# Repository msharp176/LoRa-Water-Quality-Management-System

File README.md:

# LoRa Water Quality Management System
### By Cole Hadley, Patricio Benitez Palermo, and Matthew Sharp
#### Penn State Harrisburg Senior Electrical Engineering Capstone Design Course, Fall 2025

# Project Repository Overview

This repository contains all hardware, firmware, software, and documentation associated with the gateway, sensor node, and supporting prototypes used throughout this project. The directory structure is organized to clearly separate production-ready components from prototyping artifacts, while providing comprehensive traceability for PCB designs, firmware, simulations, and supporting tools.

## Directory Structure

### **Gateway**

Code and PCB designs for the system gateway.

* **Dashboard**
  Python code for the gateway dashboard and system monitoring utilities.

* **LoRa Receiver**
  PCB design files, RP2350 firmware, and a console-logging Python script for a dedicated LoRa receiver module.

* **Neural Network**
  Code and related resources for the neural network implementation used in the system.

---

### **Prototyping and Testing**

Various PCB designs and test code used during early prototyping and validation phases.

---

### **Sensor Node**

Master directory for the final Sensor Node design, including PCB files, firmware, documentation, and test artifacts.

#### **Code**

Production firmware implementation for the Sensor Node.

* **Bin**
  Final binary executable for the RP2350 microcontroller (`.uf2`).

* **Lib**
  Custom-implemented C drivers for the sensor node.

  * **sx126x**: Semtech-provided driver files with custom HAL and radio ISR implementations.

* **Stash**
  Top-level gateway/node firmware source files. These are not included in the build unless a file is manually integrated into `main.c`.

* **Sys_Utils**
  Abstracted system-level modules, including LoRa communications, RDT3.0 implementation, and other project-specific utilities.

* **Tests**
  Code used to validate custom drivers and subsystem behaviors.

#### **Docs**

Datasheets, PCB design write-ups, and annotated Bill-of-Materials (BOM) for the final Sensor Node PCB.

#### **PCB Layout**

Complete KiCAD implementation of the sensor node PCB.

#### **Simulation**

Simulation files and output results for the analyses performed during development.

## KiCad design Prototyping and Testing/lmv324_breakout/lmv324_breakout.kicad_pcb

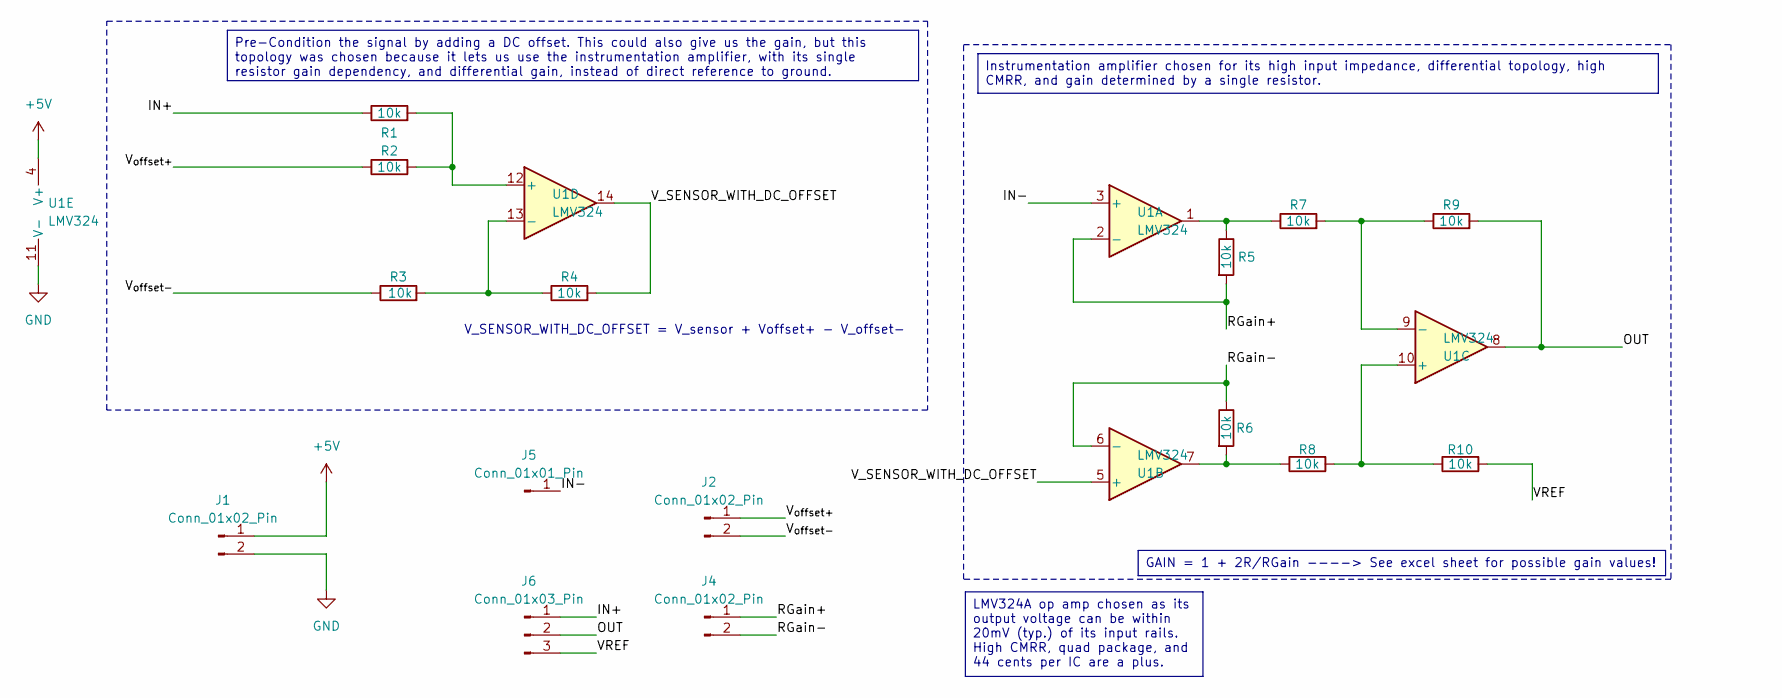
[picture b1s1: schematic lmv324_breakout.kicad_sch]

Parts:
J1, J2, J4: Conn_01x02_Pin; PinHeader_1x02_P2.54mm_Vertical
J5: Conn_01x01_Pin; PinHeader_1x01_P2.54mm_Vertical
J6: Conn_01x03_Pin; PinHeader_1x03_P2.54mm_Vertical
R1, R2, R3, R4, R5, R6, R7, R8, R9, R10: 10k; R_0805_2012Metric_Pad1.20x1.40mm_HandSolder
U1: LMV324; TSSOP-14_4.4x5mm_P0.65mm

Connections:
+5V: J1.1, U1.4 (V+)
/IN+: J6.1, R1.1
/IN-: J5.1, U1.3 (+)
/OUT: J6.2, R9.2, U1.8
/RGain+: J4.1, R5.2, U1.2 (-)
/RGain-: J4.2, R6.1, U1.6 (-)
/VREF: J6.3, R10.2
/V_SENSOR_WITH_DC_OFFSET: R4.2, U1.5 (+), U1.14
/V_{offset+}: J2.1, R2.1
/V_{offset-}: J2.2, R3.1
GND: J1.2, U1.11 (V-)
unnamed: R5.1, R7.1, U1.1
unnamed: R6.2, R8.1, U1.7
unnamed: R8.2, R10.1, U1.10 (+)
unnamed: R7.2, R9.1, U1.9 (-)
unnamed: R1.2, R2.2, U1.12 (+)
unnamed: R3.2, R4.1, U1.13 (-)

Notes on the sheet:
V_SENSOR_WITH_DC_OFFSET = V_sensor + Voffset+ - V_offset-
Instrumentation amplifier chosen for its high input impedance, differential topology, high CMRR, and gain determined by a single resistor.
Pre-Condition the signal by adding a DC offset. This could also give us the gain, but this topology was chosen because it lets us use the instrumentation amplifier, with its single resistor gain dependency, and differential gain, instead of direct reference to ground.
LMV324A op amp chosen as its output voltage can be within 20mV (typ.) of its input rails. High CMRR, quad package, and 44 cents per IC are a plus.
GAIN = 1 + 2R/RGain ----> See excel sheet for possible gain values!

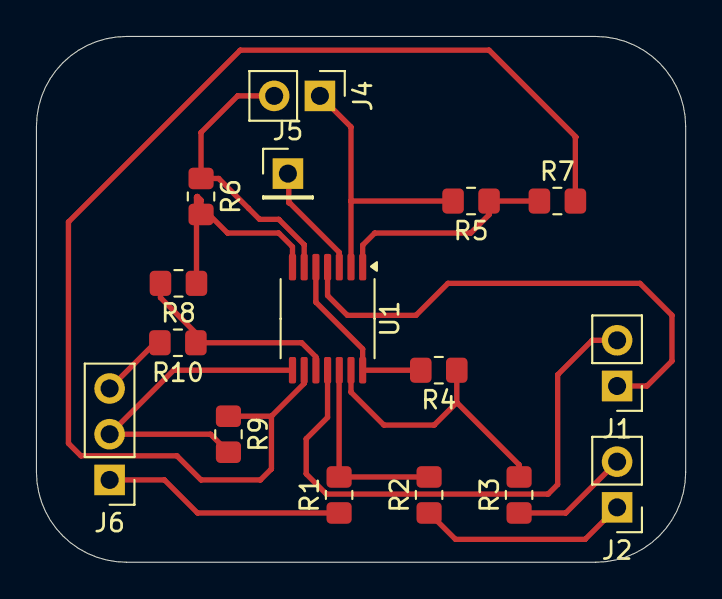
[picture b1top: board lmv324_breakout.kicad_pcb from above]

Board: 2 copper layers, 36.1 x 29.2 mm, 16 parts (0 on the bottom side), 17 nets.

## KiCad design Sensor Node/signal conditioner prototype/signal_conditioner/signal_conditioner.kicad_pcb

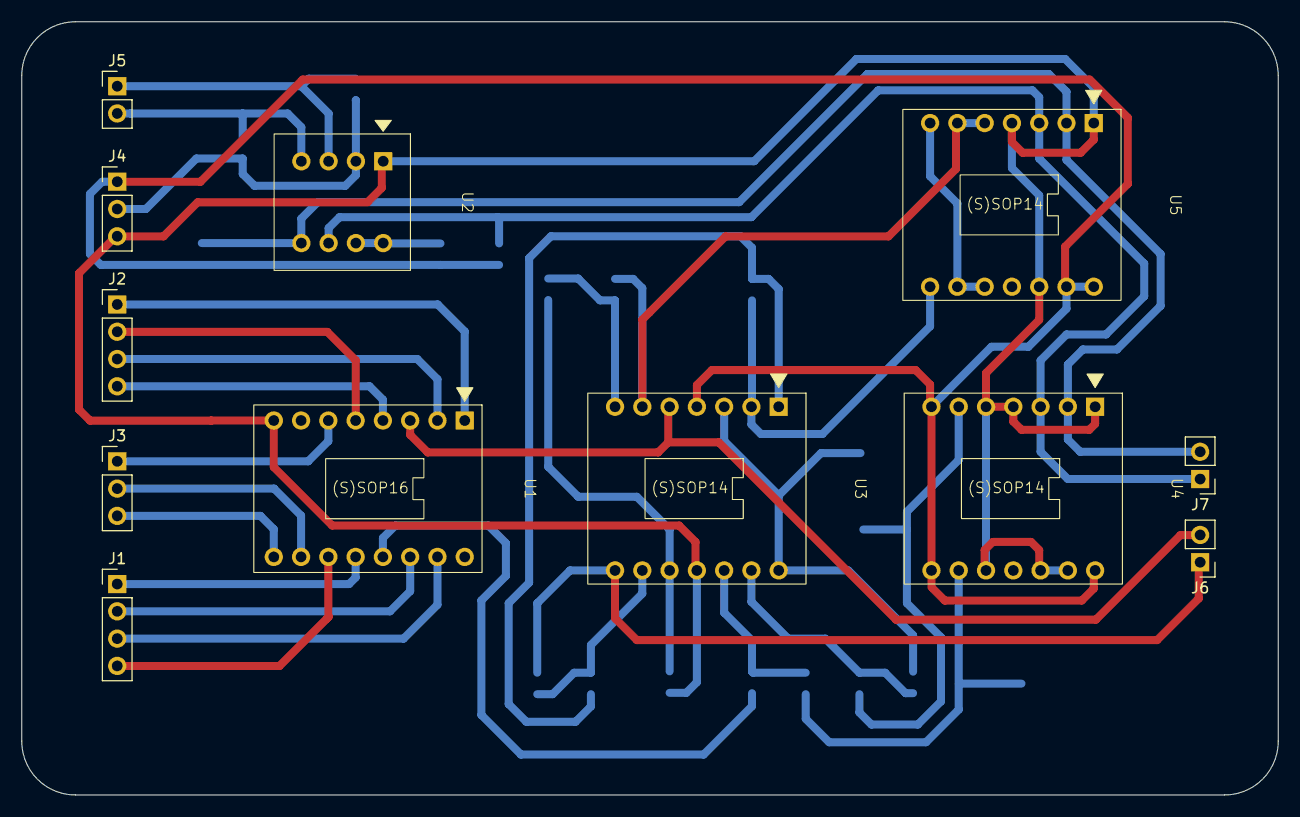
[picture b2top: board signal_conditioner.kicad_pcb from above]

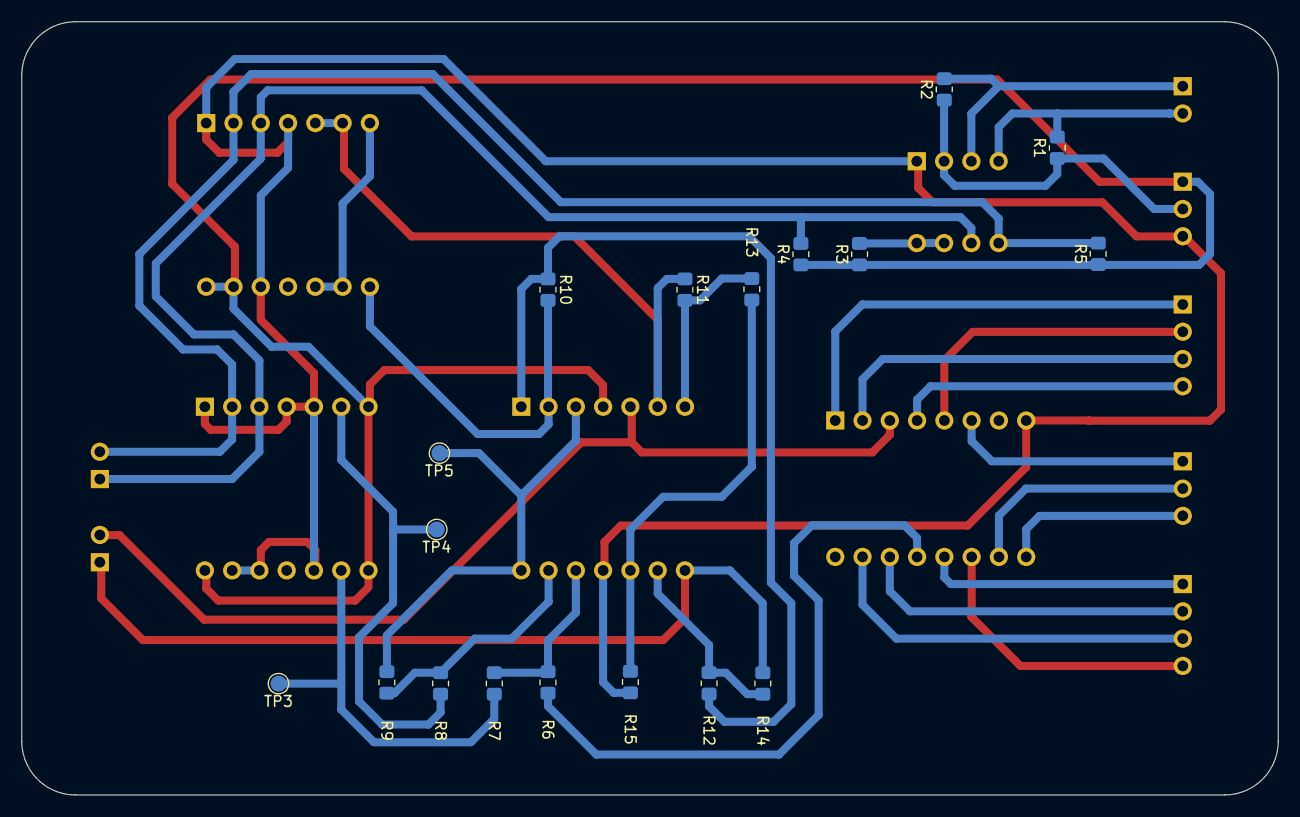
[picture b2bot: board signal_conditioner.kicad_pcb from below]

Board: 2 copper layers, 117.0 x 72.0 mm, 30 parts (18 on the bottom side), 34 nets.

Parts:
J1, J2: Conn_01x04_Pin; PinHeader_1x04_P2.54mm_Vertical
J3, J4: Conn_01x03_Pin; PinHeader_1x03_P2.54mm_Vertical
J5, J6, J7: Conn_01x02_Pin; PinHeader_1x02_P2.54mm_Vertical
R1, R2, R4, R5: 4k; R_0805_2012Metric_Pad1.20x1.40mm_HandSolder
R3: 200k; R_0805_2012Metric_Pad1.20x1.40mm_HandSolder
R6, R7, R8, R9, R10, R11, R12, R13, R14, R15: 10k; R_0805_2012Metric_Pad1.20x1.40mm_HandSolder
TP3, TP4, TP5: TestPoint_Small; TestPoint_Pad_D1.5mm
U1: TMUX1309; (S)SOP16
U2: LSF0102; (S)SOP8
U3: LMV324; (S)SOP14
U4, U5: MCP4651T-503E_ST; (S)SOP14

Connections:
+3V3: J4.2, R1.1, R2.1, U2.2 (Vref_{A})
+5V: J4.1, R3.1, R4.1, R5.1, U3.4 (V+), U4.7 (P1A), U4.8 (P0A), U4.14 (VDD), U5.13 (A1), U5.14 (VDD)
/I2C_SCL_{1}: J5.2, R1.2, U2.4 (A_{2})
/I2C_SCL_{1}_5V: J7.2, R5.2, U2.5 (B2), U4.2 (SCL), U5.2 (SCL)
/I2C_SDA_{1}: J5.1, R2.2, U2.3 (A_{1})
/I2C_SDA_{1}_5V: J7.1, R4.2, U2.6 (B1), U4.3 (SDA), U5.3 (SDA)
/OUT+: J6.1, R14.2, U3.8
/OUT-: J6.2, U1.3 (DB), U3.5 (+)
/S0A: J1.1, U1.12 (S0A)
/S0B: J2.1, U1.1 (S0B)
/S1A: J1.2, U1.14 (S1A)
/S1B: J2.2, U1.5 (S1B)
/S2A: J1.3, U1.15 (S2A)
/S2B: J2.3, U1.2 (S2B)
/S3A: J1.4, U1.11 (S3A)
/S3B: J2.4, U1.4 (S3B)
/SEL0: J3.2, U1.10 (A0)
/SEL1: J3.3, U1.9 (A1)
/SEN+: R6.1, U1.13 (DA)
/Software Defined Instrumentation Amplifier/RGain+: R10.2, U3.2 (-), U5.8 (P0A)
/Software Defined Instrumentation Amplifier/RGain-: R11.1, U3.6 (-), U5.5 (P1B), U5.6 (P1W)
/Software Defined Instrumentation Amplifier/V_SENSOR_WITH_DC_OFFSET: R9.2, TP5.1, U3.3 (+), U3.14
/Software Defined Instrumentation Amplifier/V_{offset+}: R7.1, TP3.1, U4.9 (P0W)
/Software Defined Instrumentation Amplifier/V_{offset-}: R8.1, TP4.1, U4.6 (P1W)
/~EN: J3.1, U1.6 (~EN)
GND: J4.3, R15.2, U1.8 (GND), U2.1 (GND), U3.11 (V-), U4.1 (HVC/A0), U4.4 (VSS), U4.5 (P1B), U4.10 (P0B), U4.12 (A2), U4.13 (A1), U5.1 (HVC/A0), U5.4 (VSS), U5.12 (A2)
unnamed: R10.1, R12.1, U3.1
unnamed: R11.2, R13.1, U3.7
unnamed: R3.2, U2.7 (Vref_{B}), U2.8 (EN)
unnamed: R13.2, R15.1, U3.10 (+)
unnamed: R12.2, R14.1, U3.9 (-)
unnamed: R6.2, R7.2, U3.12 (+)
unnamed: R8.2, R9.1, U3.13 (-)
unnamed: U5.7 (P1A), U5.9 (P0W), U5.10 (P0B)

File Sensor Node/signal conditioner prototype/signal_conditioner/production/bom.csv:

Designator,Footprint,Quantity,Value,LCSC Part #
"J1, J2",PinHeader_1x04_P2.54mm_Vertical,2,Conn_01x04_Pin,
"J3, J4",PinHeader_1x03_P2.54mm_Vertical,2,Conn_01x03_Pin,
"J5, J6, J7",PinHeader_1x02_P2.54mm_Vertical,3,Conn_01x02_Pin,
"R1, R2, R4, R5",0805,4,4k,
"R10, R11, R12, R13, R14, R15, R6, R7, R8, R9",0805,10,10k,
R3,0805,1,200k,
"TP3, TP4, TP5",TestPoint_Pad_D1.5mm,3,TestPoint_Small,
U1,(S)SOP16,1,TMUX1309,
U2,(S)SOP8,1,LSF0102,
U3,(S)SOP14,1,LMV324,
"U4, U5",(S)SOP14,2,MCP4651T-503E_ST,

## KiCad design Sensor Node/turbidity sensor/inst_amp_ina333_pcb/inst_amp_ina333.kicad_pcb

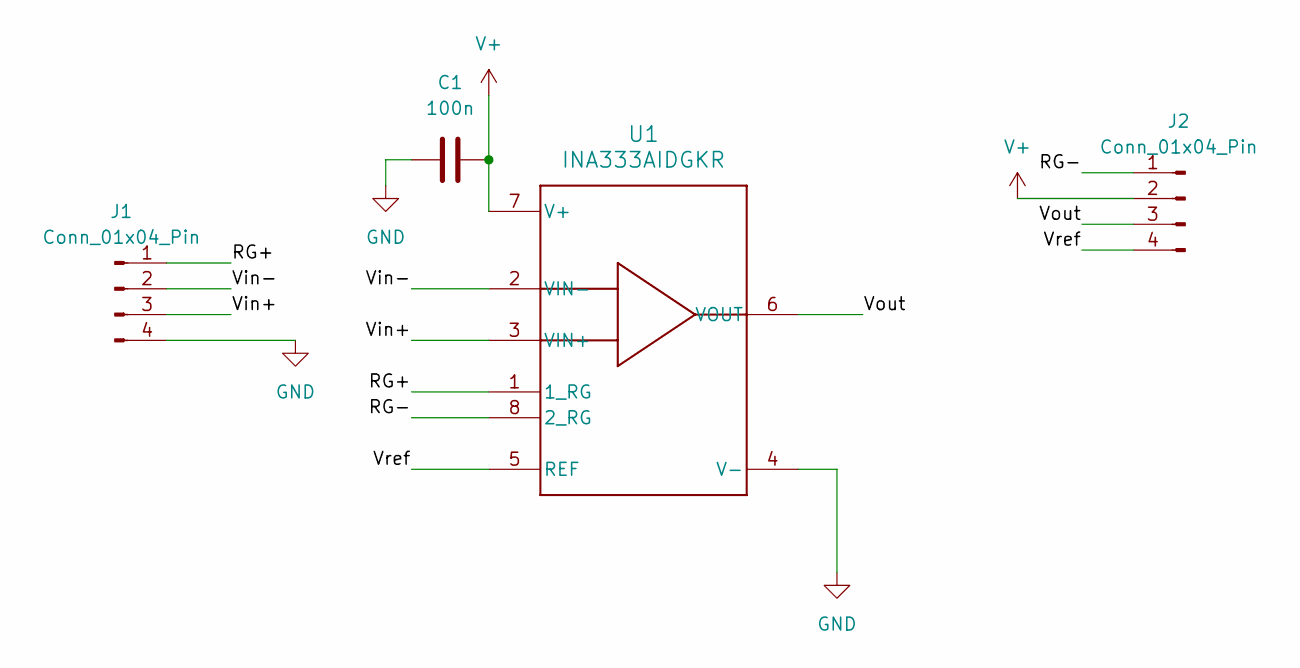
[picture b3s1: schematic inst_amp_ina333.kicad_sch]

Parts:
C1: 100n; C_1206_3216Metric
J1, J2: Conn_01x04_Pin; PinHeader_1x04_P2.54mm_Vertical
U1: INA333AIDGKR; INA333_VSSOP

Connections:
/RG+: J1.1, U1.1 (1_RG)
/RG-: J2.1, U1.8 (2_RG)
/Vin+: J1.3, U1.3 (VIN+)
/Vin-: J1.2, U1.2 (VIN-)
/Vout: J2.3, U1.6 (VOUT)
/Vref: J2.4, U1.5 (REF)
GND: C1.1, J1.4, U1.4 (V-)
V+: C1.2, J2.2, U1.7 (V+)

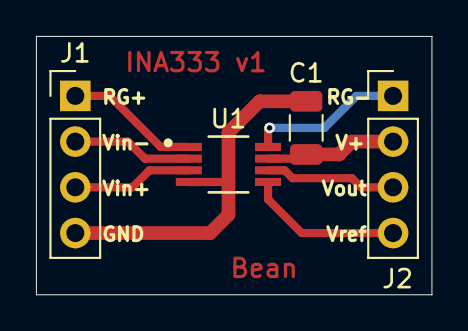
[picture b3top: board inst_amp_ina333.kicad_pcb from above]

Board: 2 copper layers, 22.0 x 14.4 mm, 4 parts (0 on the bottom side), 8 nets.

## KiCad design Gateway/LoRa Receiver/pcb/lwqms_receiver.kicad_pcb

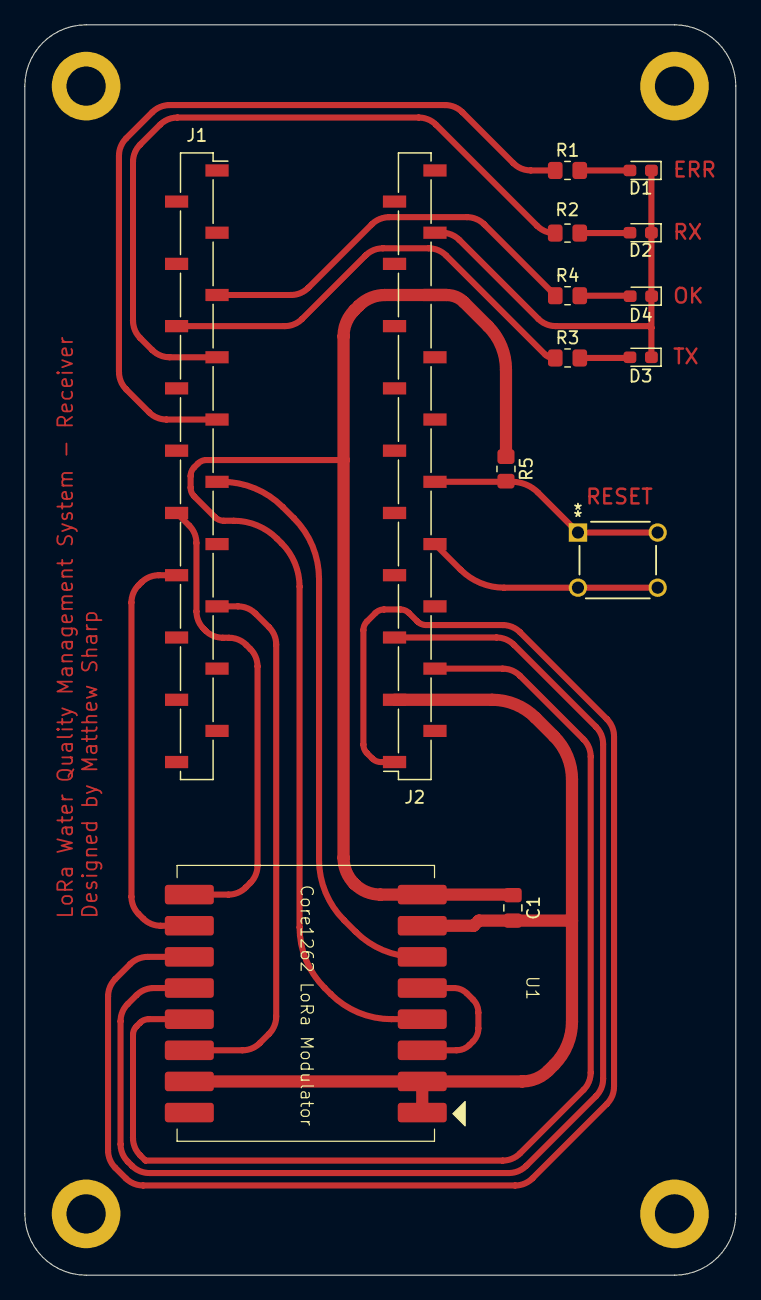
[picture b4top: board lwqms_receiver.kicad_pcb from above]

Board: 2 copper layers, 58.0 x 102.0 mm, 14 parts (0 on the bottom side), 21 nets.

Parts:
C1: 100n; C_0805_2012Metric_Pad1.18x1.45mm_HandSolder
D1, D2, D3, D4: LED; LED_0603_1608Metric_Pad1.05x0.95mm_HandSolder
J1, J2: Conn_01x20; PinSocket_1x20_P2.54mm_Vertical_SMD_Pin1Right
R1: 75R; R_0805_2012Metric_Pad1.20x1.40mm_HandSolder
R2, R3, R4: 165R; R_0805_2012Metric_Pad1.20x1.40mm_HandSolder
R5: 10k; R_0805_2012Metric_Pad1.20x1.40mm_HandSolder
SW1: Tactile Pushbutton; SW4_1825910-B_TEC
U1: Core1262 HF; Core1262

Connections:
+3V3: C1.1, J2.16, R5.1, U1.4 (TXEN), U1.8 (V_{DD})
/ERR_LED: J1.9, R1.1
/LoRa_BUSY: J1.12, U1.9 (BUSY)
/LoRa_CS: J1.15, U1.14 (~CS)
/LoRa_IRQ: J1.11, U1.6 (DIO1)
/LoRa_~RESET: J1.14, U1.10 (~RESET)
/RX_LED: J1.7, R2.1
/SPI_MISO_{0}: J2.1, U1.11 (MISO)
/SPI_MOSI_{0}: J2.5, U1.12 (MOSI)
/SPI_SCK_{0}: J2.4, U1.13 (SCK)
/STATUS_LED: J1.5, R4.1
/TX_LED: J1.6, R3.1
GND: C1.2, J2.3, U1.1 (GND), U1.2 (GND), U1.7 (GND), U1.15 (GND)
GND1: J2.8, SW1.3 (B1), SW1.4 (B2)
GND2: D1.1 (K), D2.1 (K), D3.1 (K), D4.1 (K), J2.18
unnamed: D1.2 (A), R1.2
unnamed: D2.2 (A), R2.2
unnamed: D3.2 (A), R3.2
unnamed: D4.2 (A), R4.2
unnamed: J2.10, R5.2, SW1.1 (A1), SW1.2 (A2)
unnamed: U1.3 (RXEN), U1.5 (DIO2)

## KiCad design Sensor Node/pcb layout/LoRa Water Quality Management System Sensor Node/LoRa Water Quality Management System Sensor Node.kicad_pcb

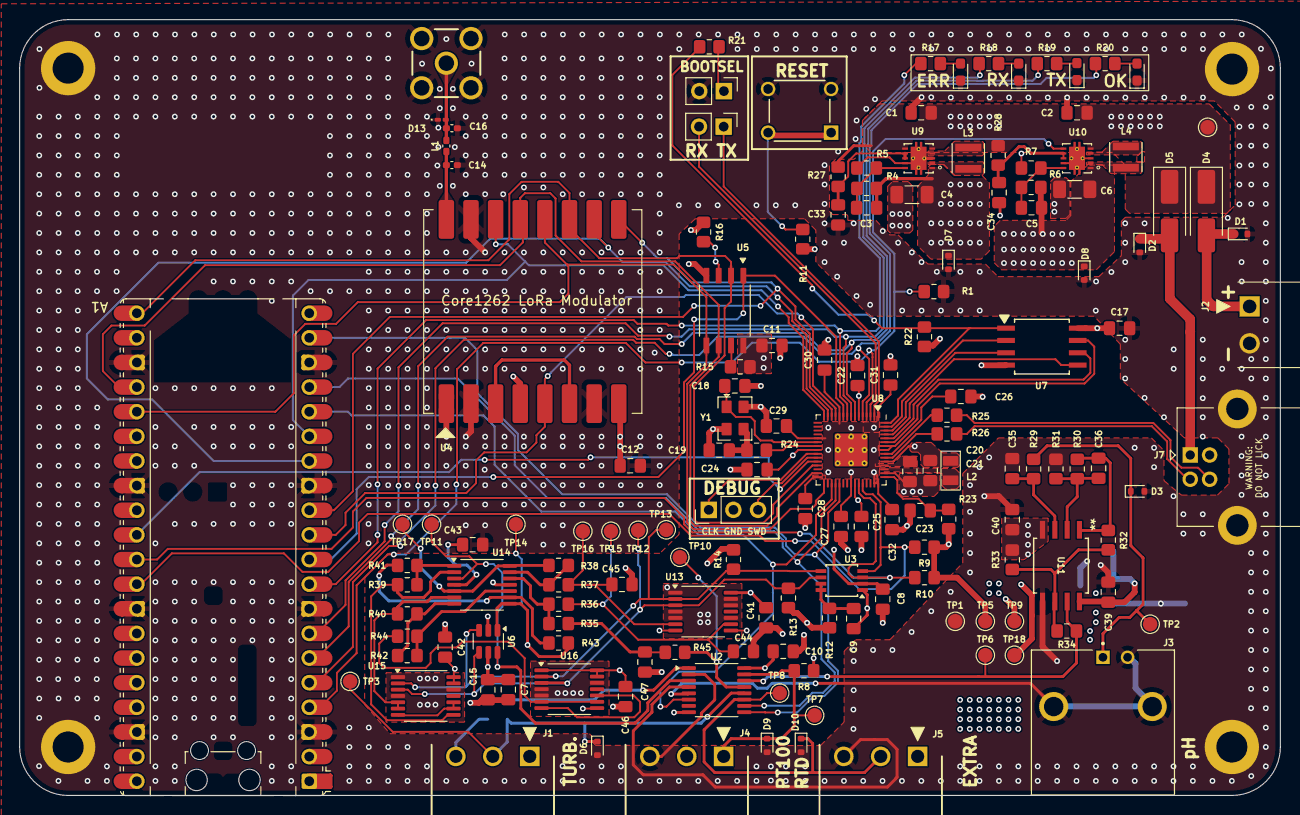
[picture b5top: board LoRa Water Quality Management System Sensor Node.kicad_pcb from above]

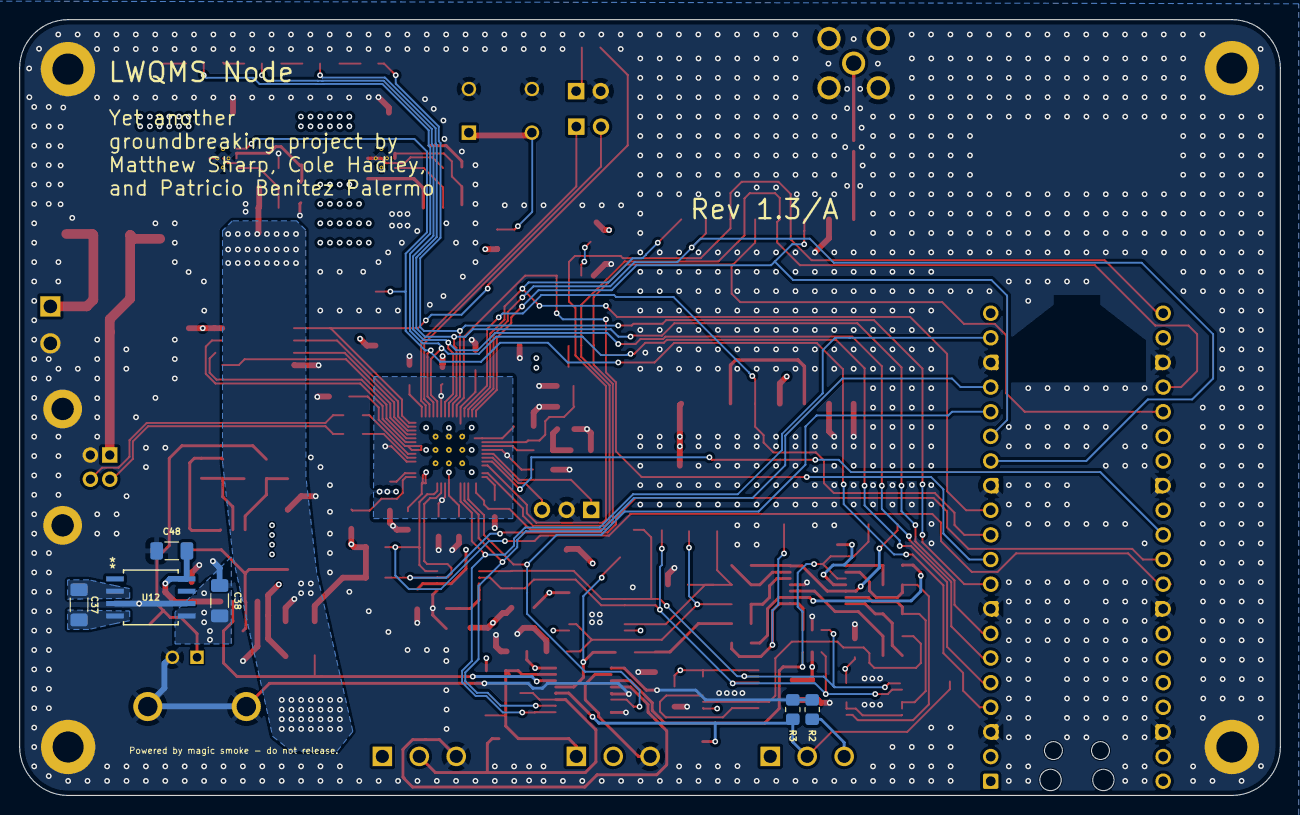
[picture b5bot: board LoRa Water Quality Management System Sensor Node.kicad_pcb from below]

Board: 4 copper layers, 130.0 x 80.0 mm, 157 parts (6 on the bottom side), 96 nets.

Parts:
A1: RaspberryPi_Pico; RaspberryPi_Pico_Common_Unspecified
C1, C2: 22uF; C_0805_2012Metric_Pad1.18x1.45mm_HandSolder
C3: 4p; C_0805_2012Metric_Pad1.18x1.45mm_HandSolder
C4, C6: 47uF; C_1206_3216Metric_Pad1.33x1.80mm_HandSolder
C5: 2.4p; C_0805_2012Metric_Pad1.18x1.45mm_HandSolder
C7, C20, C21, C23, C24: 4.7u; C_0805_2012Metric_Pad1.18x1.45mm_HandSolder
C8, C9, C10, C11, C12, C15, C17, C22, C25, C26, C27, C28, C29, C30, C31, C32, C33, C34, C39, C40, C41, C42, C43, C44, C45, C46, C47: 100n; C_0805_2012Metric_Pad1.18x1.45mm_HandSolder
C14, C16: C; C_0402_1005Metric_Pad0.74x0.62mm_HandSolder
C18, C19: 15p; C_0805_2012Metric_Pad1.18x1.45mm_HandSolder
C35: 2.2n; C_0805_2012Metric_Pad1.18x1.45mm_HandSolder
C36: 1u; C_0805_2012Metric_Pad1.18x1.45mm_HandSolder
C37, C38, C48: 100u; C_1206_3216Metric_Pad1.33x1.80mm_HandSolder
D1, D2, D3, D6, D8, D9, D10: T5V0S5A-7; D_SOD-523
D4, D5: B240AE-13; D_SMA_Handsoldering
D7: T3V3S5A-7; D_SOD-523
D11, D12, D14, D15: LED; LED_0603_1608Metric_Pad1.05x0.95mm_HandSolder
D13: ESDARF02-1BU2CK; D_0201_0603Metric_Pad0.64x0.40mm_HandSolder
J1, J4, J5: OQ0332510000G
J2: OQ0232510000G
J3: CONBNC002; LINX_CONBNC002
J6, J9: Conn_01x02; PinHeader_1x02_P2.54mm_Vertical
J7: USB_B; USB_B_Lumberg_2411_02_Horizontal
J8: SMA-J-P-X-RA-TH1; SAMTEC_SMA-J-P-X-RA-TH1
J10: Conn_01x03; PinHeader_1x03_P2.54mm_Vertical
L1: L; L_0402_1005Metric_Pad0.77x0.64mm_HandSolder
L2: 3.3u; AOTA-B201610S3R3-101-T
L3, L4: 2.2uH; IND_LQH3NPZ2R2MMEL
R1, R5, R7: 100k; R_0805_2012Metric_Pad1.20x1.40mm_HandSolder
R2: 0R; R_0805_2012Metric_Pad1.20x1.40mm_HandSolder
R3, R8: 4.7k; R_0805_2012Metric_Pad1.20x1.40mm_HandSolder
R4: 560k; R_0805_2012Metric_Pad1.20x1.40mm_HandSolder
R6: 910k; R_0805_2012Metric_Pad1.20x1.40mm_HandSolder
R9, R10, R13, R14, R21, R24: 1k; R_0805_2012Metric_Pad1.20x1.40mm_HandSolder
R11, R15, R16, R22, R30, R31, R33, R39, R40, R41, R42, R43, R44: 10k; R_0805_2012Metric_Pad1.20x1.40mm_HandSolder
R12: 200k; R_0805_2012Metric_Pad1.20x1.40mm_HandSolder
R17: 75R; R_0805_2012Metric_Pad1.20x1.40mm_HandSolder
R18, R19, R20: 165R; R_0805_2012Metric_Pad1.20x1.40mm_HandSolder
R23: 33R; R_0805_2012Metric_Pad1.20x1.40mm_HandSolder
R25, R26: 27R; R_0805_2012Metric_Pad1.20x1.40mm_HandSolder
R27, R28, R45: 100R; R_0805_2012Metric_Pad1.20x1.40mm_HandSolder
R29: 4.7M; R_0805_2012Metric_Pad1.20x1.40mm_HandSolder
R32, R34: 4.99k; R_0805_2012Metric_Pad1.20x1.40mm_HandSolder
R35, R36, R37, R38: 3.3M; R_0805_2012Metric_Pad1.20x1.40mm_HandSolder
SW1: Tactile Pushbutton; SW4_1825910-B_TEC
TP1, TP2, TP3, TP4, TP5, TP6, TP7, TP8, TP9, TP10, TP11, TP12, TP13, TP14: TestPoint; TestPoint_Pad_D1.5mm
TP15, TP16, TP17, TP18: TestPoint_Small; TestPoint_Pad_D1.5mm
U2: TMUX1309; TSSOP-16_4.4x5mm_P0.65mm
U3: LSF0102; TSSOP-8_3x3mm_P0.65mm
U4: Core1262 HF; Core1262
U5: MX25L3233FM2I-08Q; SOIC127P790X216-8N
U6: MCP3425Axx-xCH; SOT-23-6
U7: W25Q128JVSIQ TR; SOIC_208MIL_WIN-M
U8: RP2350_60QFN; RP2350-QFN-60-1EP_7x7_P0.4mm_EP3.4x3.4mm_ThermalVias
U9, U10: TPS63000; CONV_TPS63000DRCR
U11: TL082; SOIC_208MIL_WIN-M
U12: LM2660MX; SOIC_208MIL_WIN-M
U13, U15, U16: MCP4651T-503E_ST; TSSOP-14_4.4x5mm_P0.65mm
U14: TLV9144; TSSOP-14_4.4x5mm_P0.65mm
Y1: ABM8-272-T3

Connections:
+1V1: C21.1, C22.1, C24.1, C25.1, L2.1, U8.6 (DVDD), U8.23 (DVDD), U8.39 (DVDD), U8.50 (VREG_FB)
+3V3: A1.39 (VSYS), C3.1, C4.1, C8.1, C11.1, C12.1, C17.1, C20.1, C26.1, C27.1, C28.1, C29.1, C30.1, C31.1, C32.1, D7.1 (K), R4.1, R9.1, R10.1, R11.1, R15.1, R16.1, R22.1, R23.1, TP5.1, U3.2 (Vref_{A}), U4.4 (TXEN), U4.8 (V_{DD}), U5.8 (V_{CC}), U7.8 (VCC), U8.1 (IOVDD), U8.11 (IOVDD), U8.20 (IOVDD), U8.30 (IOVDD), U8.38 (IOVDD), U8.44 (ADC_AVDD), U8.45 (IOVDD), U8.49 (VREG_VIN), U8.53 (USB_OTP_VDD), U8.54 (QSPI_IOVDD), U9.1 (VOUT)
+5V: C5.1, C6.1, C7.1, C10.1, C15.1, C39.1, C41.2, C42.2, C43.1, C46.2, C48.1, D8.1 (K), J1.1, J5.1, R6.1, R8.1, R12.1, R13.1, R14.1, TP9.1, U2.16 (V_{DD}), U6.5 (V_{DD}), U10.1 (VOUT), U11.8 (V+), U12.8 (V+), U13.7 (P1A), U13.8 (P0A), U13.14 (VDD), U14.4 (V+), U15.13 (A1), U15.14 (VDD), U16.1 (HVC/A0), U16.8 (P0A), U16.13 (A1), U16.14 (VDD)
/5V_EN: A1.4 (GPIO2), R1.1, U8.4 (GPIO2), U10.6 (EN)
/Buck-Boost Regulator Layout1/FB: C5.2, R6.2, R7.1, U10.10 (FB)
/Buck-Boost Regulator Layout/FB: C3.2, R4.2, R5.1, U9.10 (FB)
/ERR_LED: A1.9 (GPIO6), R17.1, U8.9 (GPIO6)
/EXTRA_IN: D10.1 (K), J5.2, TP8.1, U2.11 (S3A)
/I2C_SCL_{1}: A1.32 (GPIO27_ADC1), R9.2, U3.4 (A_{2}), U8.41 (GPIO27_ADC1)
/I2C_SCL_{1}_5V: R14.2, TP13.1, U3.5 (B2), U6.3 (SCL), U13.2 (SCL), U15.2 (SCL), U16.2 (SCL)
/I2C_SDA_{1}: A1.31 (GPIO26_ADC0), R10.2, U3.3 (A_{1}), U8.40 (GPIO26_ADC0)
/I2C_SDA_{1}_5V: R13.2, TP12.1, U3.6 (B1), U6.4 (SDA), U13.3 (SDA), U15.3 (SDA), U16.3 (SDA)
/LoRa_BUSY: A1.12 (GPIO9), U4.9 (BUSY), U8.13 (GPIO9)
/LoRa_CS: A1.15 (GPIO11), U4.14 (~CS), U8.15 (GPIO11)
/LoRa_IRQ: A1.11 (GPIO8), U4.5 (DIO1), U8.12 (GPIO8)
/LoRa_~RESET: A1.14 (GPIO10), U4.10 (~RESET), U8.14 (GPIO10)
/MCU/QSPI_SCLK: U7.6 (CLK), U8.56 (QSPI_SCLK)
/MCU/QSPI_SD0: U7.5 (DI(IO0)), U8.57 (QSPI_SD0)
/MCU/QSPI_SD1: U7.2 (DO(IO1)), U8.59 (QSPI_SD1)
/MCU/QSPI_SD2: U7.3 (IO2), U8.58 (QSPI_SD2)
/MCU/QSPI_SD3: U7.7 (IO3), U8.55 (QSPI_SD3)
/MCU/QSPI_SS: R21.2, R22.2, U7.1 (~CS), U8.60 (QSPI_SS)
/MCU/SWCLK: J10.1, U8.24 (SWCLK)
/MCU/SWD: J10.3, U8.25 (SWD)
/MCU/VREG_AVDD: C23.1, R23.2, U8.46 (VREG_AVDD)
/MCU/VREG_LX: L2.2, U8.48 (VREG_LX)
/MCU/~RESET: A1.30 (RUN), R11.2, SW1.1 (A1), SW1.2 (A2), U8.26 (RUN)
/PH Sensor Pre-Amplifier ALT/-5V: C38.2, C40.2, R33.1, TP18.1, U11.4 (V-), U12.5 (OUT)
/PH_IN: R34.2, TP6.1, U2.14 (S1A), U11.7
/PH_RAW: D3.1 (K), J3.1, R29.1, TP2.1
/RF_OUT: C14.1, L1.1, U4.16 (ANT)
/RTD_SEN: D9.1 (K), J4.1, R8.2, TP7.1, U2.15 (S2A)
/RX_LED: A1.7 (GPIO5), R18.1, U8.8 (GPIO5)
/SENSOR_SEL_0: A1.17 (GPIO13), U2.10 (A0), U8.34 (GPIO22)
/SENSOR_SEL_1: A1.19 (GPIO14), U2.9 (A1), U8.35 (GPIO23)
/SPI_MISO_{0}: A1.21 (GPIO16), U4.11 (MISO), U5.2 (MISO), U8.27 (GPIO16)
/SPI_MOSI_{0}: A1.25 (GPIO19), U4.12 (MOSI), U5.5 (MOSI), U8.31 (GPIO19)
/SPI_SCK_{0}: A1.24 (GPIO18), U4.13 (SCK), U5.6 (SCLK), U8.29 (GPIO18)
/STATUS_LED: A1.5 (GPIO3), R20.1, U8.5 (GPIO3)
/Software-Defined Instrumentation Amplifier/IN+: R45.1, TP10.1, U2.13 (DA)
/Software-Defined Instrumentation Amplifier/IN-: TP11.1, U2.3 (DB), U6.6 (Vin-), U14.3 (+)
/Software-Defined Instrumentation Amplifier/OUT: R43.2, TP14.1, U6.1 (Vin+), U14.8
/Software-Defined Instrumentation Amplifier/REF: R44.2, U16.6 (P1W), U16.9 (P0W)
/Software-Defined Instrumentation Amplifier/RGain+: R39.2, U14.2 (-), U15.8 (P0A)
/Software-Defined Instrumentation Amplifier/RGain-: R40.1, U14.6 (-), U15.5 (P1B), U15.6 (P1W)
/Software-Defined Instrumentation Amplifier/V_SENSOR_WITH_DC_OFFSET: R38.2, TP17.1, U14.5 (+), U14.14
/Software-Defined Instrumentation Amplifier/V_{offset+}: C44.1, R36.1, TP15.1, U13.9 (P0W)
/Software-Defined Instrumentation Amplifier/V_{offset-}: C45.1, R37.1, TP16.1, U13.6 (P1W)
/TURB_IN: D6.1 (K), J1.2, R3.1, TP3.1, U2.12 (S0A)
/TX_LED: A1.6 (GPIO4), R19.1, U8.7 (GPIO4)
/UART_RX_{0}: A1.2 (GPIO1), J6.2, U8.3 (GPIO1)
/UART_TX_{0}: A1.1 (GPIO0), J6.1, U8.2 (GPIO0)
/USB_D+: J7.3 (D+), R25.2
/USB_D-: J7.2 (D-), R26.2
/USB_VBUS: D2.1 (K), D5.2 (A), J7.1 (VBUS)
/V_{BATT}: D1.1 (K), D4.2 (A), J2.1
/V_{IN}: C1.1, C2.1, D4.1 (K), D5.1 (K), R27.1, R28.1, TP4.1, U9.5 (VIN), U9.6 (EN), U10.5 (VIN)
/~FLASH_CS: A1.10 (GPIO7), U5.1 (~CS), U8.10 (GPIO7)
/~SENSOR_EN: A1.16 (GPIO12), U2.6 (~EN), U8.33 (GPIO21)
GND: A1.3 (GND), A1.8 (GND), A1.13 (GND), A1.18 (GND), A1.23 (GND), A1.28 (GND), A1.33 (AGND), A1.38 (GND), C1.2, C2.2, C4.2, C6.2, C7.2, C8.2, C9.2, C10.2, C11.2, C12.2, C14.2, C15.2, C16.2, C17.2, C18.1, C19.1, C20.2, C21.2, C22.2, C23.2, C24.2, C25.2, C26.2, C27.2, C28.2, C29.2, C30.2, C31.2, C32.2, C33.2, C34.2, C35.2, C38.1, C39.2, C40.1, C41.1, C42.1, C43.2, C44.2, C45.2, C46.1, C47.2, C48.2, D1.2 (A), D2.2 (A), D3.2 (A), D6.2 (A), D7.2 (A), D8.2 (A), D9.2 (A), D10.2 (A), D11.1 (K), D12.1 (K), D13.1 (A1), D14.1 (K), D15.1 (K), J2.2, J3.2, J3.S1, J3.S2, J4.3, J5.3, J7.4 (GND), J7.5 (Shield), J8.2, J8.3, J8.4, J8.5, J9.2, J10.2, R1.2, R2.2, R3.2, R5.2, R7.2, R31.1, SW1.3 (B1), SW1.4 (B2), TP1.1, U2.1 (S0B), U2.2 (S2B), U2.4 (S3B), U2.5 (S1B), U2.8 (GND), U3.1 (GND), U4.1 (GND), U4.2 (GND), U4.7 (GND), U4.15 (GND), U5.4 (GND), U6.2 (V_{SS}), U7.4 (GND), U8.47 (VREG_PGND), U8.61 (GND), U9.3 (PGND), U9.9 (GND), U9.11 (PGND), U9.11_1 (PGND), U9.11_2 (PGND), U9.11_3 (PGND), U9.11_4 (PGND), U9.11_5 (PGND), U9.11_6 (PGND), U9.11_7 (PGND), U9.11_8 (PGND), U10.3 (PGND), U10.9 (GND), U10.11 (PGND), U10.11_1 (PGND), U10.11_2 (PGND), U10.11_3 (PGND), U10.11_4 (PGND), U10.11_5 (PGND), U10.11_6 (PGND), U10.11_7 (PGND), U10.11_8 (PGND), U11.5 (+), U12.3 (GND), U12.6 (LV), U13.1 (HVC/A0), U13.4 (VSS), U13.5 (P1B), U13.10 (P0B), U13.12 (A2), U13.13 (A1), U14.11 (V-), U15.1 (HVC/A0), U15.4 (VSS), U15.12 (A2), U16.4 (VSS), U16.5 (P1B), U16.12 (A2), Y1.2, Y1.4
unnamed: C19.2, R24.2, Y1.3
unnamed: C36.2, R30.2, R32.1, U11.1
unnamed: C47.1, R35.1, R45.2
unnamed: D11.2 (A), R17.2
unnamed: D12.2 (A), R18.2
unnamed: C16.1, D13.2 (A2), J8.1, L1.2
unnamed: D14.2 (A), R19.2
unnamed: D15.2 (A), R20.2
unnamed: J1.3, R2.1
unnamed: J9.1, R21.1
unnamed: R39.1, R41.1, U14.1
unnamed: R40.2, R42.1, U14.7
unnamed: C9.1, R12.2, U3.7 (Vref_{B}), U3.8 (EN)
unnamed: U4.3 (RXEN), U4.6 (DIO2)
unnamed: R15.2, U5.7 (~HOLD)
unnamed: R16.2, U5.3 (~WP)
unnamed: R26.1, U8.51 (USB_DM)
unnamed: R25.1, U8.52 (USB_DP)
unnamed: C18.2, U8.21 (XIN), Y1.1
unnamed: R24.1, U8.22 (XOUT)
unnamed: L3.2, U9.4 (L1)
unnamed: L3.1, U9.2 (L2)
unnamed: C33.1, R27.2, U9.7 (PS/SYNC), U9.8 (VINA)
unnamed: L4.2, U10.4 (L1)
unnamed: L4.1, U10.2 (L2)
unnamed: C34.1, R28.2, U10.7 (PS/SYNC), U10.8 (VINA)
unnamed: C35.1, R29.2, U11.3 (+)
unnamed: C36.1, R30.1, R31.2, U11.2 (-)
unnamed: R32.2, R33.2, R34.1, U11.6 (-)
unnamed: C37.1, U12.2 (CAP+)
unnamed: R42.2, R44.1, U14.10 (+)
unnamed: R41.2, R43.1, U14.9 (-)
unnamed: R35.2, R36.2, U14.12 (+)
unnamed: R37.2, R38.1, U14.13 (-)
unnamed: U15.7 (P1A), U15.9 (P0W), U15.10 (P0B)
unnamed: U16.7 (P1A), U16.10 (P0B)

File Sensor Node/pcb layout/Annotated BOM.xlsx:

Connectors
Reference | MFG P/N | Qty/Board | Unit Cost | Ext. Cost | Description | Digikey Link
J1, J4, J5 | OSTOQ033251 | 3 | 0.65 | 1.9500000000000002 | 3 Pin Connector, 3.81mm pitch | https://www.digikey.com/en/products/detail/amphenol-anytek/O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
J2 | OQ0232510000G | 1 | 0.27 | 0.27 | 2 Pin Connector, 3.81mm pitch | https://www.digikey.com/en/products/detail/amphenol-anytek/O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
J3 | CONBNC002 | 1 | 2.0499999999999998 | 2.0499999999999998 | BNC connector | https://www.digikey.com/en/products/detail/amphenol-rf/031-5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
N/A | OSTTJ0331530 | 3 | 1.88 | 5.64 | Mating connector for OQ0332510000G | https://www.digikey.com/en/products/detail/amphenol-anytek/T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
N/A | TJ0231530000G | 1 | 0.67 | 0.67 | Mating connector for OQ0232510000G | https://www.digikey.com/en/products/detail/amphenol-anytek/T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
J7 | UJ2-BH-BL1-TH | 1 | 0.51 | 0.51 | USB Type B Female Connector | https://www.digikey.com/en/products/detail/same-sky-formerly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
J8 | SMA-J-P-H-RA-TH1 | 1 | 3.43 | 3.43 | SMA antenna connector | https://www.digikey.com/en/products/detail/samtec-inc/SMA-J-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
J10 | 3 Pos. Pin Header | 1 | 0 | 0 | 3 Pos. Pin Header
J6, J9 | 2 Pos. Pin Header | 2 | 0 | 0 | 2 Pos. Pin Header
Connectors Subtotal |  |  |  | 14.52
ICs
Reference | MFG P/N | Qty/Board | Unit Cost | Ext. Cost | Description | Digikey Link
U2 | TMUX1309APWR | 1 | 0.37 | 0.37 | 2x SP4T Switch | https://www.digikey.com/en/products/detail/texas-instruments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
U3 | LSF0102DCTR | 1 | 0.43 | 0.43 | I2C Level Shifter | https://www.digikey.com/en/products/detail/texas-instruments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
U5 | MX25L3233FM2I-08Q | 1 | 0.48 | 0.48 | 32Mbit SPI Flash Memory | https://www.digikey.com/en/products/detail/macronix/MX25L323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
U6 | MCP3425A0T-E/CH | 1 | 2.48 | 2.48 | 16 Bit A/D with I2C Interface | https://www.digikey.com/en/products/detail/microchip-technol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
U7 | W25Q128JVSIQ TR | 1 | 1.85 | 1.85 | 128MBit QSPI Program Memory | https://www.digikey.com/en/products/detail/winbond-electroni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
U8 | RP2350_60QFN | 1 | 1.1000000000000001 | 1.1000000000000001 | Microcontroller | https://www.digikey.com/en/products/detail/raspberry-pi/SC15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
U9,U10 | TPS63000DRCR | 2 | 2.61 | 5.22 | 1.6A Buck-Boost Converter | https://www.digikey.com/en/products/detail/texas-instruments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
U11 | TL082CDR | 1 | 0.35 | 0.35 | JFET Input Op-Amp x 2 | https://www.digikey.com/en/products/detail/texas-instruments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
U14 | LMV324IPWR | 1 | 0.44 | 0.44 | Quad Rail-To-Rail Op-Amp | https://www.digikey.com/en/products/detail/texas-instruments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
U13,U15,U16 | MCP4651T-503E/ST | 2 | 1.24 | 2.48 | 50kOhm 2x Digital Potentiometer with I2C Interface | https://www.digikey.com/en/products/detail/microchip-technol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
ICs Subtotal |  |  |  | 15.2
Specialized Components
D4,D5 | B240AE-13 | 2 | 0.2 | 0.4 | Schottky Diode | https://www.digikey.com/en/products/detail/diodes-incorporat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
D1,D2,D3,D6,D8,D9,D10 | T5V0S5A-7 | 7 | 8.3000000000000004E-2 | 0.58100000000000007 | 5V TVS | https://www.digikey.com/en/products/detail/diodes-incorporat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
D7 | T3V3S5A-7 | 1 | 0.15 | 0.15 | 3.3V TVS | https://www.digikey.com/en/products/detail/diodes-incorporat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
D12, D14, D15 | KT EELP41.12-S2U1-25-2X4Y-5-R18 | 3 | 0.16 | 0.48 | Green LED | https://www.digikey.com/en/products/detail/ams-osram-usa-inc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
D13 | ESDARF02-1BU2CK | 1 | 0.13 | 0.13 | 3.3V 3GHz BW TVS Diode | https://www.digikey.com/en/products/detail/stmicroelectronic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
D11 | KR EELP41.22-Q1S1-36-A8J8-020-R18 | 1 | 0.14000000000000001 | 0.14000000000000001 | Red LED | https://www.digikey.com/en/products/detail/ams-osram-usa-inc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
Y1 | ABM8-272-T3 | 1 | 0.54 | 0.54 | 12MHz XTAL Oscillator | https://www.digikey.com/en/products/detail/abracon-llc/ABM8-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
L3, L4 | LQH3NPZ2R2MMEL | 2 | 0.34 | 0.68 | Buck-Boost Converter Inductor | https://www.digikey.com/en/products/detail/murata-electronic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
L2 | AOTA-B201610S3R3-101-T | 1 | 0.22 | 0.22 | RP2350 DC-DC Inductor with Guaranteed Winding Direction | https://www.digikey.com/en/products/detail/abracon-llc/AOTA-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
Specialized Components Subtotal |  |  |  | 3.3210000000000006
Components
Reference | MFG P/N | Qty/Board | Unit Cost | Ext. Cost | Description | Digikey Link
R8,R27,R28,R45 | RNCF0805DTE100R | 4 | 0.1 | 0.4 | 100R (0.5%) | https://www.digikey.com/en/products/detail/stackpole-electro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
L1, R2 | RMCF0805ZT0R00 | 2 | 0.01 | 0.02 | Jumper (qty 10. cheaper than qty. 1) | https://www.digikey.com/en/products/detail/stackpole-electro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
R12, R33 | RMCF0805FT200K | 2 | 0.1 | 0.2 | 200k | https://www.digikey.com/en/products/detail/stackpole-electro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
R11,R15,R16,R22,R35,R36,R37,R38,R39,R40,R41,R42,R43,R44 | RNCF0805DTE10K0 | 14 | 2.7E-2 | 0.378 | 10k (0.5%) | https://www.digikey.com/en/products/detail/stackpole-electro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
R21,R24,R31,R9,R10,R13,R14 | RMCF0805FT1K00 | 7 | 0.02 | 0.14000000000000001 | 1k | https://www.digikey.com/en/products/detail/stackpole-electro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
R23 | RMCF0805FT33R0 | 1 | 0.1 | 0.1 | 33R | https://www.digikey.com/en/products/detail/stackpole-electro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
R3 | RMCF0805FT4K70 | 1 | 0.1 | 0.1 | 4.7k | https://www.digikey.com/en/products/detail/stackpole-electro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
R25,R26 | RMCF0805FT27R0 | 2 | 0.1 | 0.2 | 27R | https://www.digikey.com/en/products/detail/stackpole-electro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
R17 | RMCF0805FT71R5 | 1 | 0.1 | 0.1 | 75R | https://www.digikey.com/en/products/detail/stackpole-electro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
R18,R19,R20 | RMCF0805FT160R | 3 | 0.1 | 0.30000000000000004 | 165R | https://www.digikey.com/en/products/detail/stackpole-electro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
R1,R5,R7,R32,R34 | RNCF0805BTE100K | 5 | 0.12 | 0.6 | 100k (0.1%) | https://www.digikey.com/en/products/detail/stackpole-electro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
R4 | RNCF0805DTE560K | 1 | 0.1 | 0.1 | 560k (0.5%) | https://www.digikey.com/en/products/detail/stackpole-electro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
R6 | RNCF0805DTE910K | 1 | 0.1 | 0.1 | 910k (0.5%) | https://www.digikey.com/en/products/detail/stackpole-electro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
R29 | RMCF0805FT4M70 | 1 | 0.1 | 0.1 | 4.7M | https://www.digikey.com/en/products/detail/stackpole-electro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
R30 | RMCF0805FT3K00 | 1 | 0.1 | 0.1 | 3k | https://www.digikey.com/en/products/detail/stackpole-electro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
C1,C2 | CL21A226MAYNNNE | 2 | 0.11 | 0.22 | 22uF | https://www.digikey.com/en/products/detail/samsung-electro-m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
C8,C9,C10,C11,C12,C15,C17,C22,C25,C26,C27,C28,C29,C30,C31,C32,C33,C34,C39,C40,C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 | KGM21NR71E104KT | 27 | 8.0000000000000002E-3 | 0.216 | 100n | https://www.digikey.com/en/products/detail/kyocera-avx/KGM21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
C13,C20,C21,C23,C24 | CL21A475KPFNNNE | 5 | 4.8000000000000001E-2 | 0.24 | 4.7u (qty > 10) | https://www.digikey.com/en/products/detail/samsung-electro-m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
C18,C19 | GMC21CG150J50NT | 2 | 3.3000000000000002E-2 | 6.6000000000000003E-2 | 15p (qty > 10) | https://www.digikey.com/en/products/detail/cal-chip-electron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
C35 | C0805C222K5RACTU | 1 | 0.1 | 0.1 | 2.2n | https://www.digikey.com/en/products/detail/kemet/C0805C222K5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
C36 | CL21B105KAFNNNE | 1 | 0.08 | 0.08 | 1u | https://www.digikey.com/en/products/detail/samsung-electro-m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
C37,C38,C48 | GRM31CR61A107MEA8K | 3 | 0.29899999999999999 | 0.89700000000000002 | 100u (qty > 10) | https://www.digikey.com/en/products/detail/murata-electronic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
C4,C6 | GRM31CR61A476ME15L | 2 | 0.38 | 0.76 | 47uF | https://www.digikey.com/en/products/detail/murata-electronic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
C3 | CC0805CRNPO9BN4R0 | 1 | 0.11 | 0.11 | 4p | https://www.digikey.com/en/products/detail/yageo/CC0805CRNPO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
C5 | CC0805CRNPO9BN2R4 | 1 | 0.11 | 0.11 | 2.4p | https://www.digikey.com/en/products/detail/yageo/CC0805CRNPO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
Components Subtotal |  |  |  | 5.737000000000001
Integrated Modules
Reference | MFG P/N | Qty/Board | Unit Cost | Ext. Cost | Description | Digikey Link
U4 | Core1262 HF | 1 | 7.99 | 7.99 | LoRa Modulator | https://www.waveshare.com/core1262-868m.htm
Integrated Modules Subtotal |  |  |  | 7.99
TOTAL |  |  |  | 46.768000000000001
